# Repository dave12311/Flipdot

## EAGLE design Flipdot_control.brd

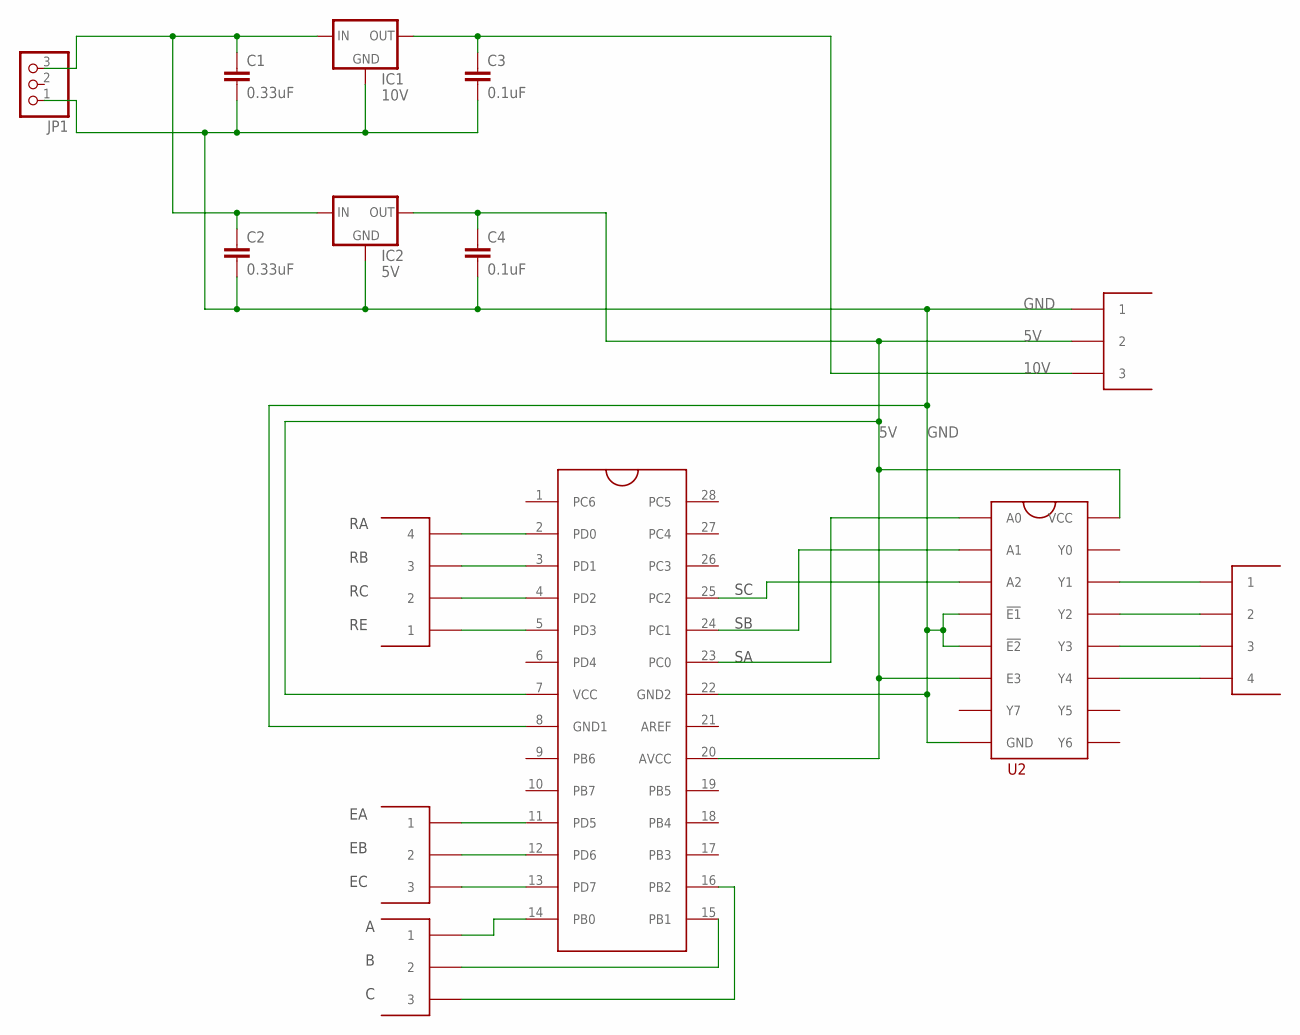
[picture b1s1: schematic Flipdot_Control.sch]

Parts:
C1, C2: 0.33uF; C025-024X044
C3, C4: 0.1uF; C025-024X044
IC1: 10V; 78XXS
IC2: 5V; 78XXS
JP1: PINHD-1X3; 1X03
U1: ATMEGA328P; DIL28
U2: 74HC238; DIL16
U$3, U$4: 4_PIN
U$5, U$6, U$7: 3_PIN

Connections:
5V: C4.1, IC2.OUT, U1.7 (VCC), U1.20 (AVCC), U2.6 (E3), U2.16 (VCC), U$7.P$2 (2)
10V: C3.1, IC1.OUT, U$7.P$3 (3)
GND: C1.2, C2.2, C3.2, C4.2, IC1.GND, IC2.GND, JP1.1, U1.8 (GND1), U1.22 (GND2), U2.4 (!E1), U2.5 (!E2), U2.8 (GND), U$7.P$1 (1)
unnamed: U2.14 (Y1), U$3.P$1 (1)
unnamed: U2.13 (Y2), U$3.P$2 (2)
unnamed: U2.12 (Y3), U$3.P$3 (3)
unnamed: U2.11 (Y4), U$3.P$4 (4)
unnamed: U1.23 (PC0), U2.1 (A0)
unnamed: U1.24 (PC1), U2.2 (A1)
unnamed: U1.25 (PC2), U2.3 (A2)
unnamed: U1.2 (PD0), U$4.P$4 (4)
unnamed: U1.3 (PD1), U$4.P$3 (3)
unnamed: U1.4 (PD2), U$4.P$2 (2)
unnamed: U1.14 (PB0), U$5.P$1 (1)
unnamed: U1.15 (PB1), U$5.P$2 (2)
unnamed: U1.16 (PB2), U$5.P$3 (3)
unnamed: U1.5 (PD3), U$4.P$1 (1)
unnamed: U1.13 (PD7), U$6.P$3 (3)
unnamed: U1.12 (PD6), U$6.P$2 (2)
unnamed: C1.1, C2.1, IC1.IN, IC2.IN, JP1.3
unnamed: U1.11 (PD5), U$6.P$1 (1)

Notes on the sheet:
A B C
RA RB RC RE
EA EB EC
SC SB SA

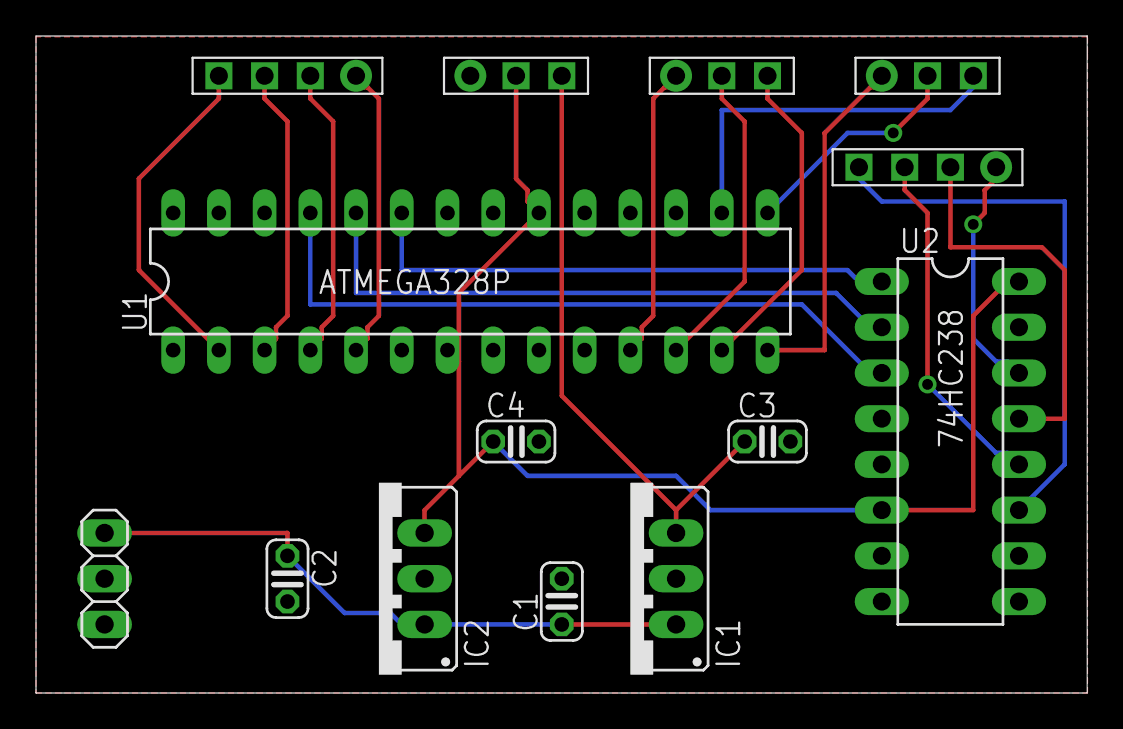
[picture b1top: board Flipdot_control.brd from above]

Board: 2 copper layers, 58.4 x 36.5 mm, 14 parts (0 on the bottom side), 21 nets.

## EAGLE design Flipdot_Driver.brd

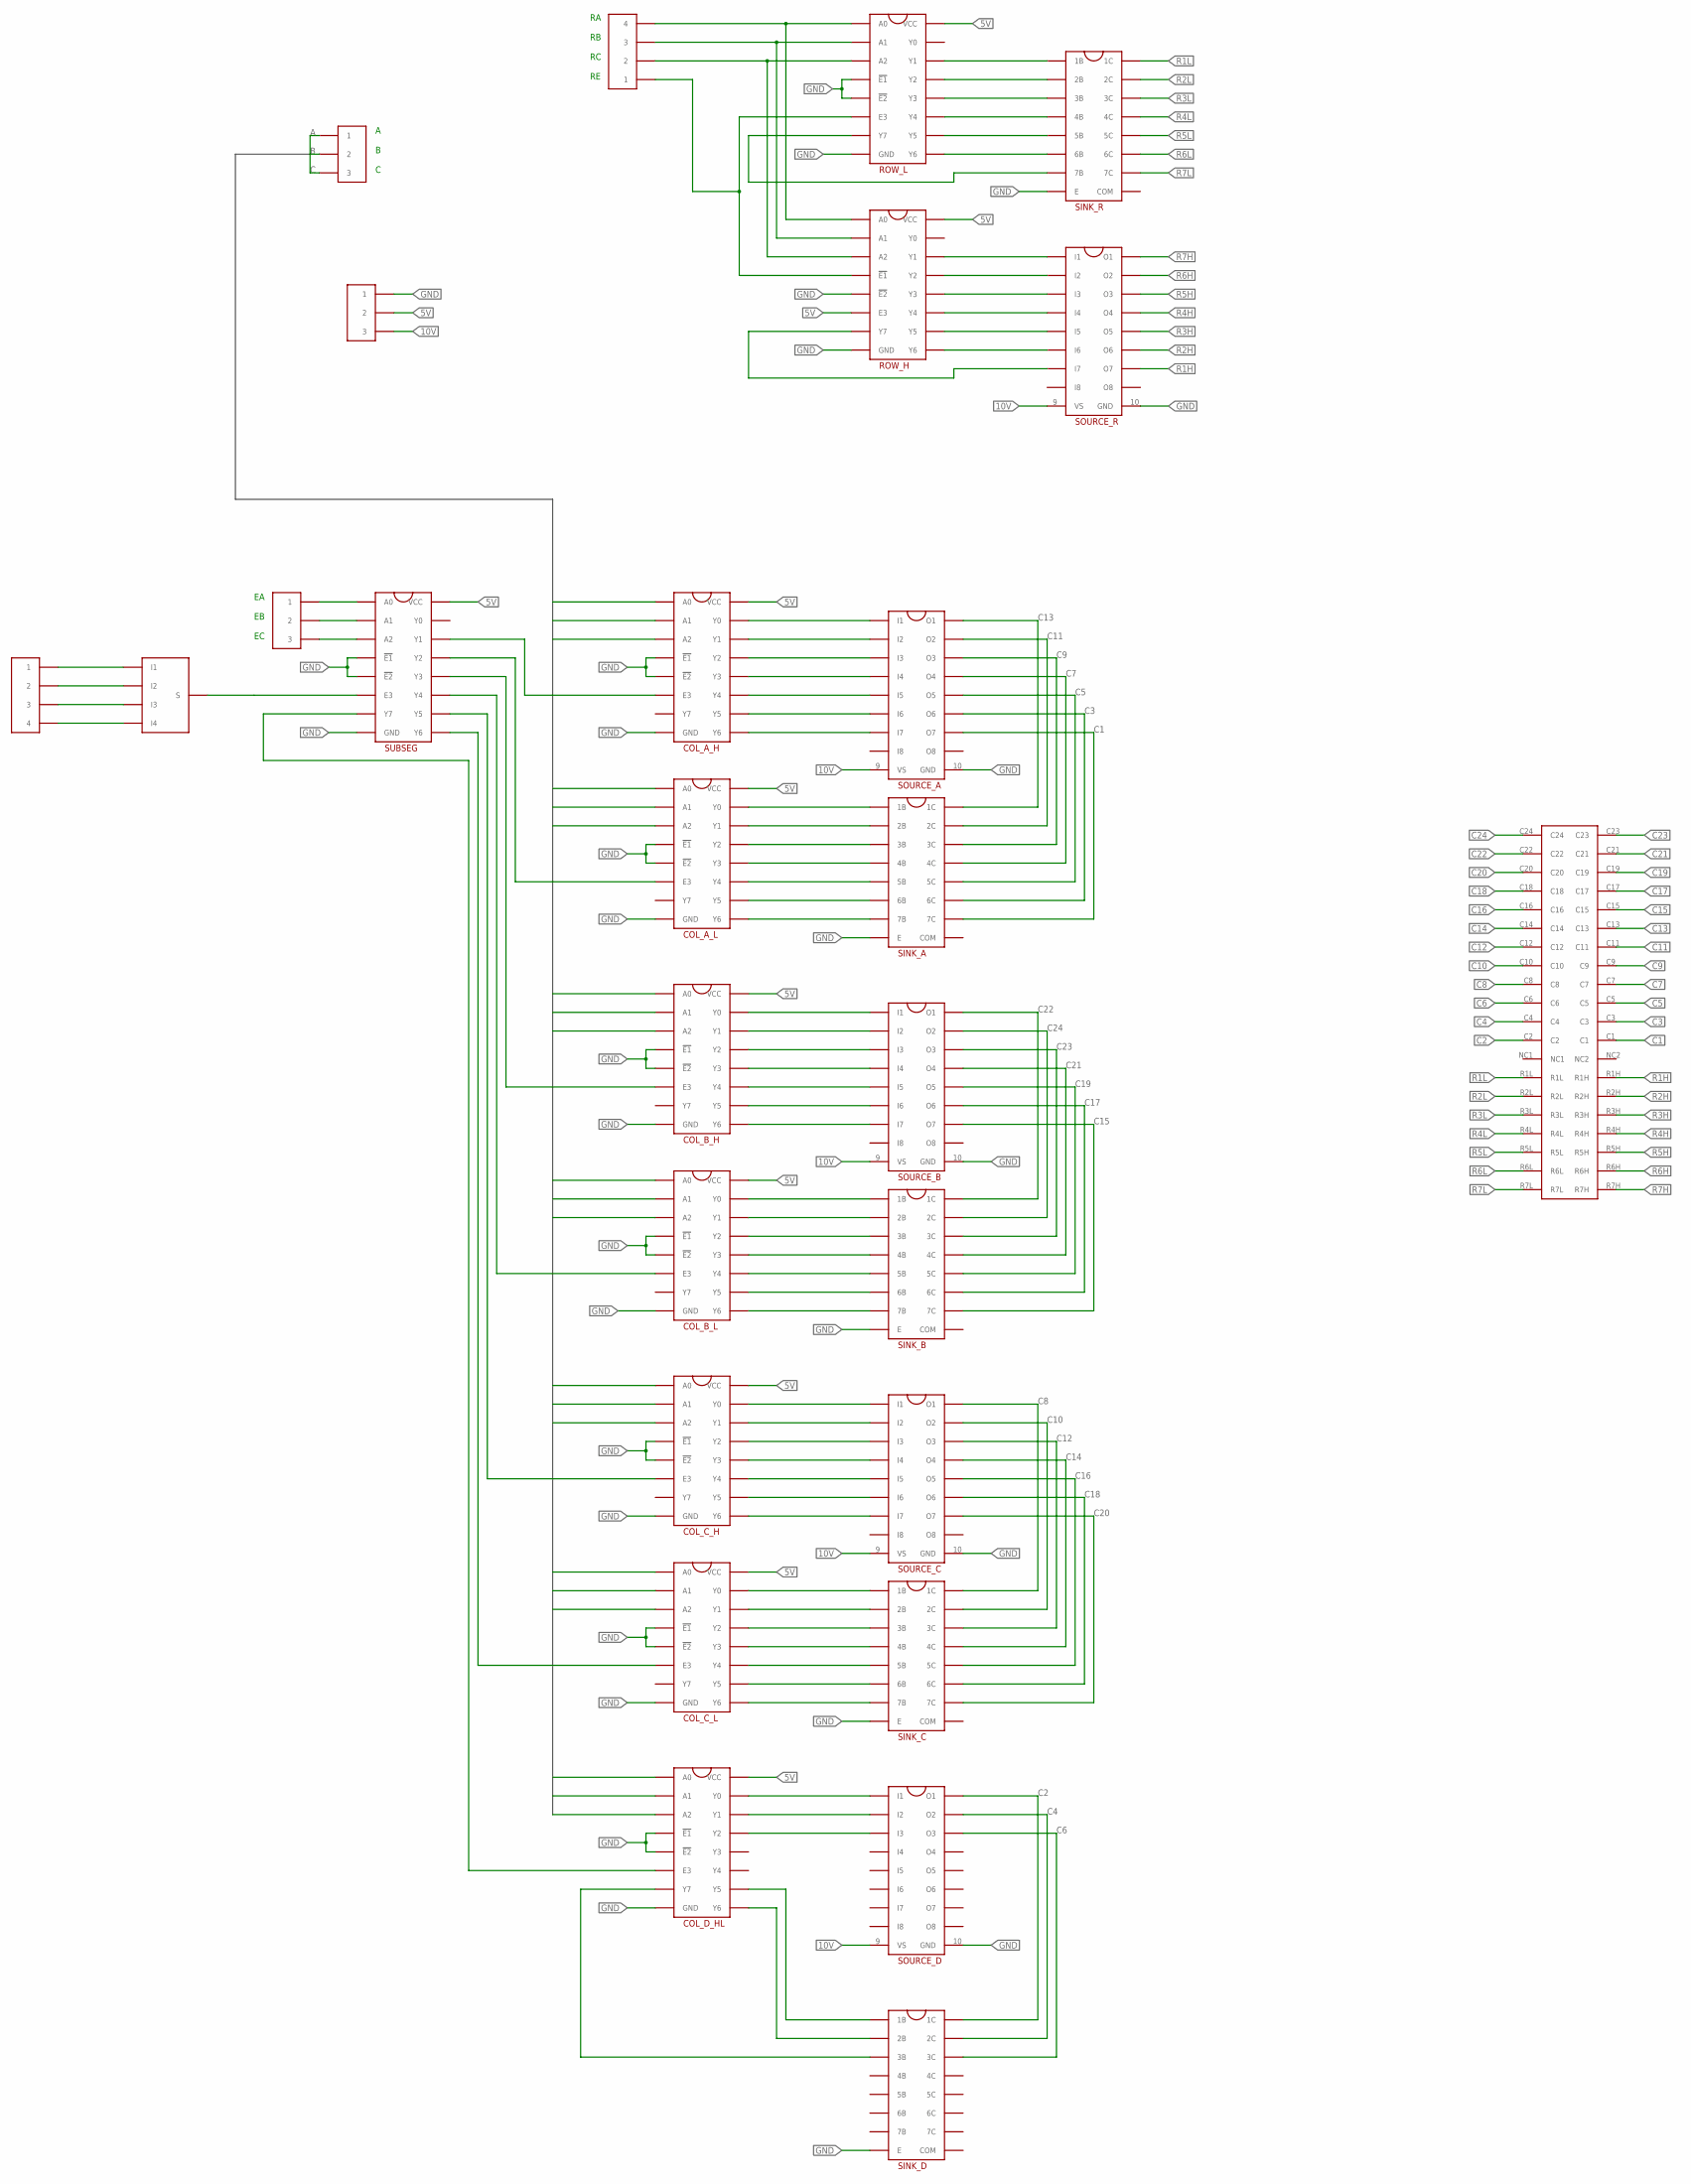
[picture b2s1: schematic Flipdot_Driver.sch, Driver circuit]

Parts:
COL_A_H: 74HC238; DIL16
COL_A_L: 74HC238; DIL16
COL_B_H: 74HC238; DIL16
COL_B_L: 74HC238; DIL16
COL_C_H: 74HC238; DIL16
COL_C_L: 74HC238; DIL16
COL_D_HL: 74HC238; DIL16
ROW_H: 74HC238; DIL16
ROW_L: 74HC238; DIL16
SINK_A: ULN2003A; DIL16
SINK_B: ULN2003A; DIL16
SINK_C: ULN2003A; DIL16
SINK_D: ULN2003A; DIL16
SINK_R: ULN2003A; DIL16
SOURCE_A: UDN2981A; DIL18
SOURCE_B: UDN2981A; DIL18
SOURCE_C: UDN2981A; DIL18
SOURCE_D: UDN2981A; DIL18
SOURCE_R: UDN2981A; DIL18
SUBSEG: 74HC238; DIL16
U$1: HEADER_40
U$2, U$3, U$5: 3_PIN
U$6, U$11: 4_PIN
U$10: JUMPER

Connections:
5V: COL_A_H.16 (VCC), COL_A_L.16 (VCC), COL_B_H.16 (VCC), COL_B_L.16 (VCC), COL_C_H.16 (VCC), COL_C_L.16 (VCC), COL_D_HL.16 (VCC), ROW_H.6 (E3), ROW_H.16 (VCC), ROW_L.16 (VCC), SUBSEG.16 (VCC), U$5.P$2 (2)
10V: SOURCE_A.9 (VS), SOURCE_B.9 (VS), SOURCE_C.9 (VS), SOURCE_D.9 (VS), SOURCE_R.9 (VS), U$5.P$3 (3)
A: COL_A_H.1 (A0), COL_A_L.1 (A0), COL_B_H.1 (A0), COL_B_L.1 (A0), COL_C_H.1 (A0), COL_C_L.1 (A0), COL_D_HL.1 (A0), U$2.P$1 (1)
B: COL_A_H.2 (A1), COL_A_L.2 (A1), COL_B_H.2 (A1), COL_B_L.2 (A1), COL_C_H.2 (A1), COL_C_L.2 (A1), COL_D_HL.2 (A1), U$2.P$2 (2)
C: COL_A_H.3 (A2), COL_A_L.3 (A2), COL_B_H.3 (A2), COL_B_L.3 (A2), COL_C_H.3 (A2), COL_C_L.3 (A2), COL_D_HL.3 (A2), U$2.P$3 (3)
C1: SINK_A.10 (7C), SOURCE_A.12 (O7), U$1.C1
C2: SINK_D.16 (1C), SOURCE_D.18 (O1), U$1.C2
C3: SINK_A.11 (6C), SOURCE_A.13 (O6), U$1.C3
C4: SINK_D.15 (2C), SOURCE_D.17 (O2), U$1.C4
C5: SINK_A.12 (5C), SOURCE_A.14 (O5), U$1.C5
C6: SINK_D.14 (3C), SOURCE_D.16 (O3), U$1.C6
C7: SINK_A.13 (4C), SOURCE_A.15 (O4), U$1.C7
C8: SINK_C.16 (1C), SOURCE_C.18 (O1), U$1.C8
C9: SINK_A.14 (3C), SOURCE_A.16 (O3), U$1.C9
C10: SINK_C.15 (2C), SOURCE_C.17 (O2), U$1.C10
C11: SINK_A.15 (2C), SOURCE_A.17 (O2), U$1.C11
C12: SINK_C.14 (3C), SOURCE_C.16 (O3), U$1.C12
C13: SINK_A.16 (1C), SOURCE_A.18 (O1), U$1.C13
C14: SINK_C.13 (4C), SOURCE_C.15 (O4), U$1.C14
C15: SINK_B.10 (7C), SOURCE_B.12 (O7), U$1.C15
C16: SINK_C.12 (5C), SOURCE_C.14 (O5), U$1.C16
C17: SINK_B.11 (6C), SOURCE_B.13 (O6), U$1.C17
C18: SINK_C.11 (6C), SOURCE_C.13 (O6), U$1.C18
C19: SINK_B.12 (5C), SOURCE_B.14 (O5), U$1.C19
C20: SINK_C.10 (7C), SOURCE_C.12 (O7), U$1.C20
C21: SINK_B.13 (4C), SOURCE_B.15 (O4), U$1.C21
C22: SINK_B.16 (1C), SOURCE_B.18 (O1), U$1.C22
C23: SINK_B.14 (3C), SOURCE_B.16 (O3), U$1.C23
C24: SINK_B.15 (2C), SOURCE_B.17 (O2), U$1.C24
GND: COL_A_H.4 (!E1), COL_A_H.5 (!E2), COL_A_H.8 (GND), COL_A_L.4 (!E1), COL_A_L.5 (!E2), COL_A_L.8 (GND), COL_B_H.4 (!E1), COL_B_H.5 (!E2), COL_B_H.8 (GND), COL_B_L.4 (!E1), COL_B_L.5 (!E2), COL_B_L.8 (GND), COL_C_H.4 (!E1), COL_C_H.5 (!E2), COL_C_H.8 (GND), COL_C_L.4 (!E1), COL_C_L.5 (!E2), COL_C_L.8 (GND), COL_D_HL.4 (!E1), COL_D_HL.5 (!E2), COL_D_HL.8 (GND), ROW_H.5 (!E2), ROW_H.8 (GND), ROW_L.4 (!E1), ROW_L.5 (!E2), ROW_L.8 (GND), SINK_A.8 (E), SINK_B.8 (E), SINK_C.8 (E), SINK_D.8 (E), SINK_R.8 (E), SOURCE_A.10 (GND), SOURCE_B.10 (GND), SOURCE_C.10 (GND), SOURCE_D.10 (GND), SOURCE_R.10 (GND), SUBSEG.4 (!E1), SUBSEG.5 (!E2), SUBSEG.8 (GND), U$5.P$1 (1)
unnamed: U$10.S1 (I1), U$11.P$1 (1)
unnamed: U$10.S2 (I2), U$11.P$2 (2)
unnamed: U$10.S3 (I3), U$11.P$3 (3)
unnamed: SUBSEG.1 (A0), U$3.P$1 (1)
unnamed: SUBSEG.2 (A1), U$3.P$2 (2)
unnamed: SUBSEG.3 (A2), U$3.P$3 (3)
unnamed: COL_A_L.6 (E3), SUBSEG.13 (Y2)
unnamed: COL_B_H.6 (E3), SUBSEG.12 (Y3)
unnamed: COL_A_H.6 (E3), SUBSEG.14 (Y1)
unnamed: COL_B_L.6 (E3), SUBSEG.11 (Y4)
unnamed: COL_C_H.6 (E3), SUBSEG.10 (Y5)
unnamed: COL_C_L.6 (E3), SUBSEG.9 (Y6)
unnamed: COL_D_HL.6 (E3), SUBSEG.7 (Y7)
unnamed: COL_A_H.15 (Y0), SOURCE_A.1 (I1)
unnamed: COL_A_H.14 (Y1), SOURCE_A.2 (I2)
unnamed: COL_A_H.13 (Y2), SOURCE_A.3 (I3)
unnamed: COL_A_H.12 (Y3), SOURCE_A.4 (I4)
unnamed: COL_A_H.11 (Y4), SOURCE_A.5 (I5)
unnamed: COL_A_H.10 (Y5), SOURCE_A.6 (I6)
unnamed: COL_A_H.9 (Y6), SOURCE_A.7 (I7)
unnamed: COL_B_H.15 (Y0), SOURCE_B.1 (I1)
unnamed: COL_B_H.14 (Y1), SOURCE_B.2 (I2)
unnamed: COL_B_H.13 (Y2), SOURCE_B.3 (I3)
unnamed: COL_B_H.12 (Y3), SOURCE_B.4 (I4)
unnamed: COL_B_H.11 (Y4), SOURCE_B.5 (I5)
unnamed: COL_B_H.10 (Y5), SOURCE_B.6 (I6)
unnamed: COL_B_H.9 (Y6), SOURCE_B.7 (I7)
unnamed: COL_C_H.15 (Y0), SOURCE_C.1 (I1)
unnamed: COL_C_H.14 (Y1), SOURCE_C.2 (I2)
unnamed: COL_C_H.13 (Y2), SOURCE_C.3 (I3)
unnamed: COL_C_H.12 (Y3), SOURCE_C.4 (I4)
unnamed: COL_C_H.11 (Y4), SOURCE_C.5 (I5)
unnamed: COL_C_H.10 (Y5), SOURCE_C.6 (I6)
unnamed: COL_C_H.9 (Y6), SOURCE_C.7 (I7)
unnamed: COL_D_HL.15 (Y0), SOURCE_D.1 (I1)
unnamed: COL_D_HL.14 (Y1), SOURCE_D.2 (I2)
unnamed: COL_D_HL.13 (Y2), SOURCE_D.3 (I3)
unnamed: COL_A_L.15 (Y0), SINK_A.1 (1B)
unnamed: COL_A_L.14 (Y1), SINK_A.2 (2B)
unnamed: COL_A_L.13 (Y2), SINK_A.3 (3B)
unnamed: COL_A_L.12 (Y3), SINK_A.4 (4B)
unnamed: COL_A_L.11 (Y4), SINK_A.5 (5B)
unnamed: COL_A_L.10 (Y5), SINK_A.6 (6B)
unnamed: COL_A_L.9 (Y6), SINK_A.7 (7B)
unnamed: COL_B_L.15 (Y0), SINK_B.1 (1B)
unnamed: COL_B_L.14 (Y1), SINK_B.2 (2B)
unnamed: COL_B_L.13 (Y2), SINK_B.3 (3B)
unnamed: COL_B_L.12 (Y3), SINK_B.4 (4B)
unnamed: COL_B_L.11 (Y4), SINK_B.5 (5B)
unnamed: COL_B_L.10 (Y5), SINK_B.6 (6B)
unnamed: COL_B_L.9 (Y6), SINK_B.7 (7B)
unnamed: COL_C_L.15 (Y0), SINK_C.1 (1B)
unnamed: COL_C_L.14 (Y1), SINK_C.2 (2B)
unnamed: COL_C_L.13 (Y2), SINK_C.3 (3B)
unnamed: COL_C_L.12 (Y3), SINK_C.4 (4B)
unnamed: COL_C_L.11 (Y4), SINK_C.5 (5B)
unnamed: COL_C_L.10 (Y5), SINK_C.6 (6B)
unnamed: COL_C_L.9 (Y6), SINK_C.7 (7B)
unnamed: COL_D_HL.10 (Y5), SINK_D.1 (1B)
unnamed: COL_D_HL.9 (Y6), SINK_D.2 (2B)
unnamed: COL_D_HL.7 (Y7), SINK_D.3 (3B)
unnamed: ROW_H.1 (A0), ROW_L.1 (A0), U$6.P$4 (4)
unnamed: ROW_H.2 (A1), ROW_L.2 (A1), U$6.P$3 (3)
unnamed: ROW_H.3 (A2), ROW_L.3 (A2), U$6.P$2 (2)
unnamed: ROW_H.4 (!E1), ROW_L.6 (E3), U$6.P$1 (1)
unnamed: ROW_L.14 (Y1), SINK_R.1 (1B)
unnamed: ROW_L.13 (Y2), SINK_R.2 (2B)
unnamed: ROW_L.12 (Y3), SINK_R.3 (3B)
unnamed: ROW_L.11 (Y4), SINK_R.4 (4B)
unnamed: ROW_L.10 (Y5), SINK_R.5 (5B)
unnamed: ROW_L.9 (Y6), SINK_R.6 (6B)
unnamed: ROW_L.7 (Y7), SINK_R.7 (7B)
unnamed: ROW_H.14 (Y1), SOURCE_R.1 (I1)
unnamed: ROW_H.13 (Y2), SOURCE_R.2 (I2)
unnamed: ROW_H.12 (Y3), SOURCE_R.3 (I3)
unnamed: ROW_H.11 (Y4), SOURCE_R.4 (I4)
unnamed: ROW_H.10 (Y5), SOURCE_R.5 (I5)
unnamed: ROW_H.9 (Y6), SOURCE_R.6 (I6)
unnamed: ROW_H.7 (Y7), SOURCE_R.7 (I7)
unnamed: U$10.S4 (I4), U$11.P$4 (4)
R1H: SOURCE_R.12 (O7), U$1.R1H
R1L: SINK_R.16 (1C), U$1.R1L
R2H: SOURCE_R.13 (O6), U$1.R2H
R2L: SINK_R.15 (2C), U$1.R2L
R3H: SOURCE_R.14 (O5), U$1.R3H
R3L: SINK_R.14 (3C), U$1.R3L
R4H: SOURCE_R.15 (O4), U$1.R4H
R4L: SINK_R.13 (4C), U$1.R4L
R5H: SOURCE_R.16 (O3), U$1.R5H
R5L: SINK_R.12 (5C), U$1.R5L
R6H: SOURCE_R.17 (O2), U$1.R6H
R6L: SINK_R.11 (6C), U$1.R6L
R7H: SOURCE_R.18 (O1), U$1.R7H
R7L: SINK_R.10 (7C), U$1.R7L
SEG_1: SUBSEG.6 (E3), U$10.X1 (S), U$10.X2 (S), U$10.X3 (S), U$10.X4 (S)

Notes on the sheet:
A B C
RA RB RC RE
EA EB EC

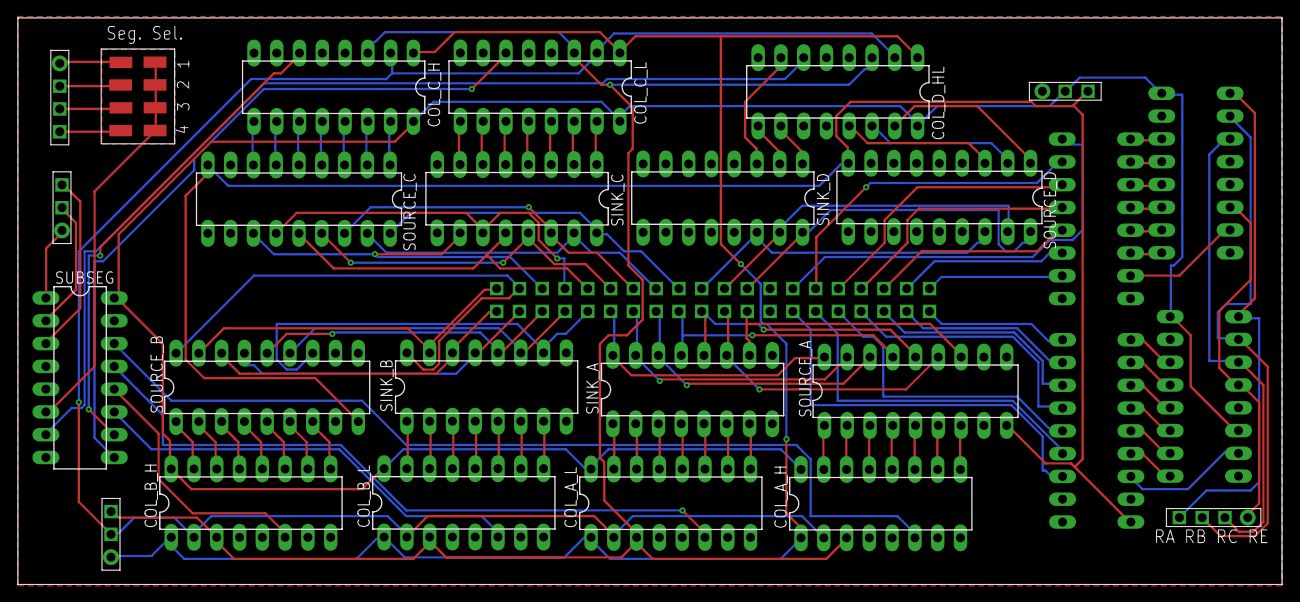
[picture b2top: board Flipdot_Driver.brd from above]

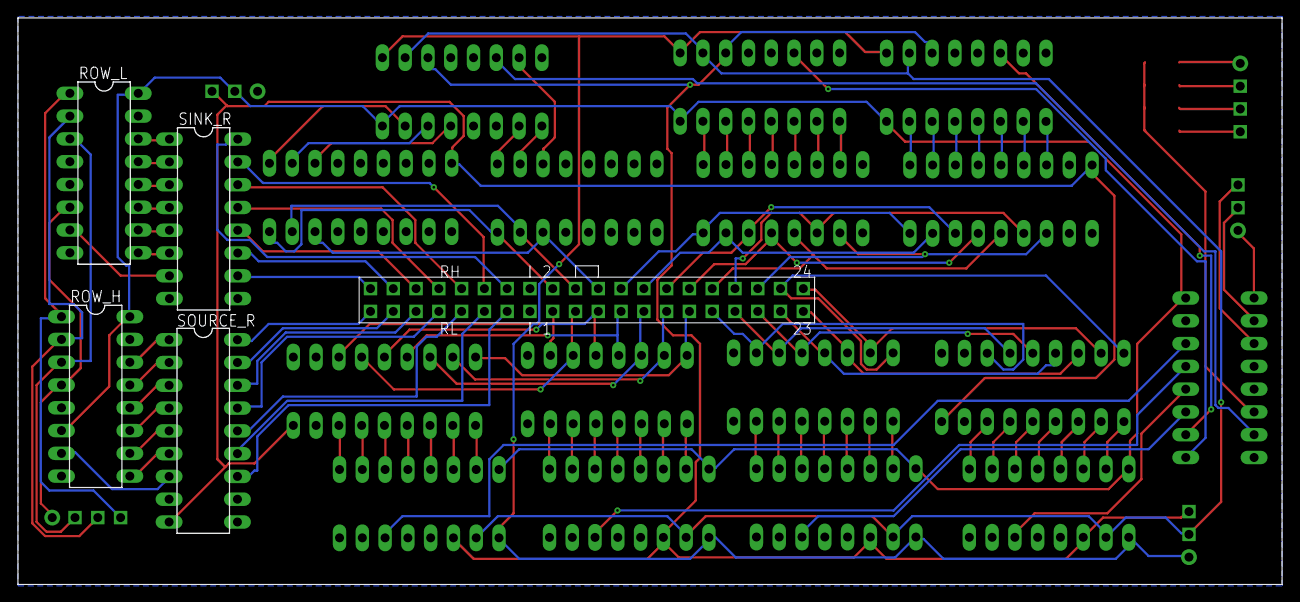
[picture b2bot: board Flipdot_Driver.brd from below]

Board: 2 copper layers, 140.9 x 63.2 mm, 27 parts (5 on the bottom side), 125 nets.

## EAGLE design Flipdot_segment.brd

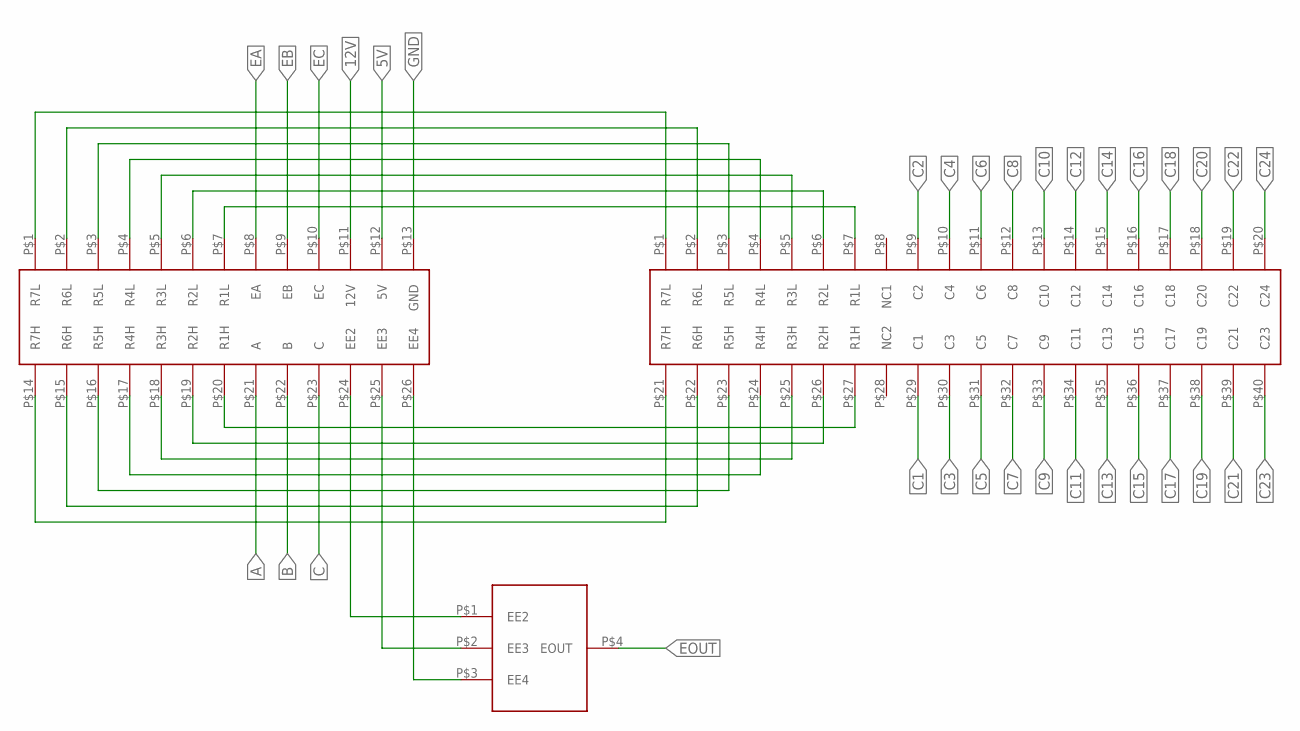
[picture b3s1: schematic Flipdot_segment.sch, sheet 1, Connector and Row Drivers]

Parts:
J1: HEADER
J2: HEADER_26
J3: JUMPER

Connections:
5V: J2.P$12 (5V); also elsewhere on the board
12V: J2.P$11 (12V); also elsewhere on the board
A: J2.P$21 (A); also elsewhere on the board
B: J2.P$22 (B); also elsewhere on the board
C: J2.P$23 (C); also elsewhere on the board
C1: J1.P$29 (C1); also elsewhere on the board
C2: J1.P$9 (C2); also elsewhere on the board
C3: J1.P$30 (C3); also elsewhere on the board
C4: J1.P$10 (C4); also elsewhere on the board
C5: J1.P$31 (C5); also elsewhere on the board
C6: J1.P$11 (C6); also elsewhere on the board
C7: J1.P$32 (C7); also elsewhere on the board
C8: J1.P$12 (C8); also elsewhere on the board
C9: J1.P$33 (C9); also elsewhere on the board
C10: J1.P$13 (C10); also elsewhere on the board
C11: J1.P$34 (C11); also elsewhere on the board
C12: J1.P$14 (C12); also elsewhere on the board
C13: J1.P$35 (C13); also elsewhere on the board
C14: J1.P$15 (C14); also elsewhere on the board
C15: J1.P$36 (C15); also elsewhere on the board
C16: J1.P$16 (C16); also elsewhere on the board
C17: J1.P$37 (C17); also elsewhere on the board
C18: J1.P$17 (C18); also elsewhere on the board
C19: J1.P$38 (C19); also elsewhere on the board
C20: J1.P$18 (C20); also elsewhere on the board
C21: J1.P$39 (C21); also elsewhere on the board
C22: J1.P$19 (C22); also elsewhere on the board
C23: J1.P$40 (C23); also elsewhere on the board
C24: J1.P$20 (C24); also elsewhere on the board
EA: J2.P$8 (EA); also elsewhere on the board
EB: J2.P$9 (EB); also elsewhere on the board
EC: J2.P$10 (EC); also elsewhere on the board
EE2: J2.P$24 (EE2), J3.P$1 (EE2)
EE3: J2.P$25 (EE3), J3.P$2 (EE3)
EE4: J2.P$26 (EE4), J3.P$3 (EE4)
EOUT: J3.P$4 (EOUT); also elsewhere on the board
GND: J2.P$13 (GND); also elsewhere on the board
unnamed: J1.P$7 (R1L), J2.P$7 (R1L)
unnamed: J1.P$6 (R2L), J2.P$6 (R2L)
unnamed: J1.P$5 (R3L), J2.P$5 (R3L)
unnamed: J1.P$4 (R4L), J2.P$4 (R4L)
unnamed: J1.P$3 (R5L), J2.P$3 (R5L)
unnamed: J1.P$2 (R6L), J2.P$2 (R6L)
unnamed: J1.P$1 (R7L), J2.P$1 (R7L)
unnamed: J1.P$27 (R1H), J2.P$20 (R1H)
unnamed: J1.P$26 (R2H), J2.P$19 (R2H)
unnamed: J1.P$25 (R3H), J2.P$18 (R3H)
unnamed: J1.P$24 (R4H), J2.P$17 (R4H)
unnamed: J1.P$23 (R5H), J2.P$16 (R5H)
unnamed: J1.P$22 (R6H), J2.P$15 (R6H)
unnamed: J1.P$21 (R7H), J2.P$14 (R7H)

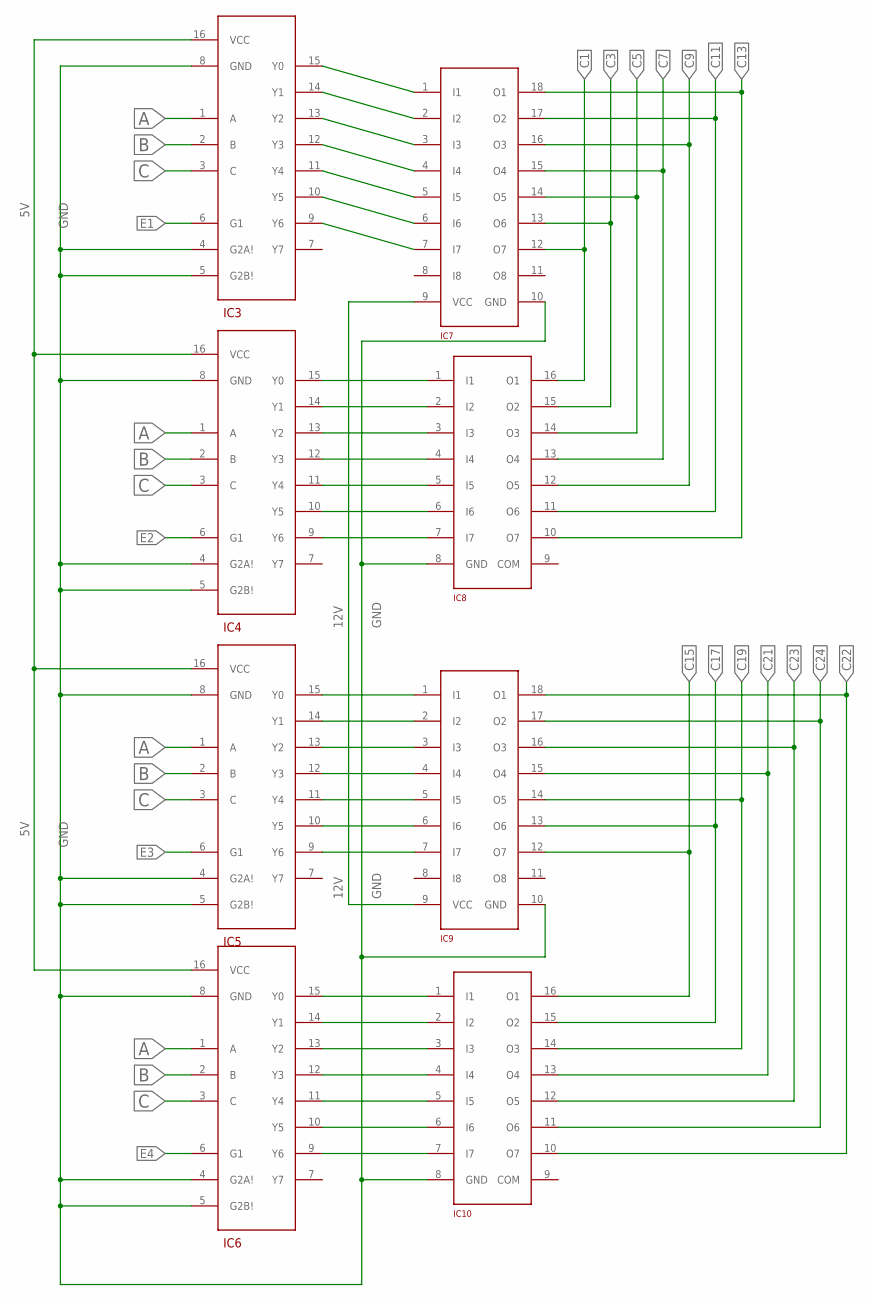
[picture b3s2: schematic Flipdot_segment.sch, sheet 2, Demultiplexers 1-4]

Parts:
IC3, IC4, IC5, IC6: M74HC238; SO16
IC7, IC9: TD62783_AFWG; SO18W
IC8, IC10: ULN2003; SO16

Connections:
5V: IC3.16 (VCC), IC4.16 (VCC), IC5.16 (VCC), IC6.16 (VCC); also elsewhere on the board
12V: IC7.9 (VCC), IC9.9 (VCC); also elsewhere on the board
A: IC3.1 (A), IC4.1 (A), IC5.1 (A), IC6.1 (A); also elsewhere on the board
B: IC3.2 (B), IC4.2 (B), IC5.2 (B), IC6.2 (B); also elsewhere on the board
C: IC3.3 (C), IC4.3 (C), IC5.3 (C), IC6.3 (C); also elsewhere on the board
C1: IC7.12 (O7), IC8.16 (O1); also elsewhere on the board
C3: IC7.13 (O6), IC8.15 (O2); also elsewhere on the board
C5: IC7.14 (O5), IC8.14 (O3); also elsewhere on the board
C7: IC7.15 (O4), IC8.13 (O4); also elsewhere on the board
C9: IC7.16 (O3), IC8.12 (O5); also elsewhere on the board
C11: IC7.17 (O2), IC8.11 (O6); also elsewhere on the board
C13: IC7.18 (O1), IC8.10 (O7); also elsewhere on the board
C15: IC9.12 (O7), IC10.16 (O1); also elsewhere on the board
C17: IC9.13 (O6), IC10.15 (O2); also elsewhere on the board
C19: IC9.14 (O5), IC10.14 (O3); also elsewhere on the board
C21: IC9.15 (O4), IC10.13 (O4); also elsewhere on the board
C22: IC9.18 (O1), IC10.10 (O7); also elsewhere on the board
C23: IC9.16 (O3), IC10.12 (O5); also elsewhere on the board
C24: IC9.17 (O2), IC10.11 (O6); also elsewhere on the board
E1: IC3.6 (G1); also elsewhere on the board
E2: IC4.6 (G1); also elsewhere on the board
E3: IC5.6 (G1); also elsewhere on the board
E4: IC6.6 (G1); also elsewhere on the board
GND: IC3.4 (G2A!), IC3.5 (G2B!), IC3.8 (GND), IC4.4 (G2A!), IC4.5 (G2B!), IC4.8 (GND), IC5.4 (G2A!), IC5.5 (G2B!), IC5.8 (GND), IC6.4 (G2A!), IC6.5 (G2B!), IC6.8 (GND), IC7.10 (GND), IC8.8 (GND), IC9.10 (GND), IC10.8 (GND); also elsewhere on the board
unnamed: IC3.15 (Y0), IC7.1 (I1)
unnamed: IC3.14 (Y1), IC7.2 (I2)
unnamed: IC3.13 (Y2), IC7.3 (I3)
unnamed: IC3.12 (Y3), IC7.4 (I4)
unnamed: IC3.11 (Y4), IC7.5 (I5)
unnamed: IC3.10 (Y5), IC7.6 (I6)
unnamed: IC3.9 (Y6), IC7.7 (I7)
unnamed: IC4.15 (Y0), IC8.1 (I1)
unnamed: IC4.14 (Y1), IC8.2 (I2)
unnamed: IC4.13 (Y2), IC8.3 (I3)
unnamed: IC4.12 (Y3), IC8.4 (I4)
unnamed: IC4.11 (Y4), IC8.5 (I5)
unnamed: IC4.10 (Y5), IC8.6 (I6)
unnamed: IC4.9 (Y6), IC8.7 (I7)
unnamed: IC5.15 (Y0), IC9.1 (I1)
unnamed: IC5.14 (Y1), IC9.2 (I2)
unnamed: IC5.13 (Y2), IC9.3 (I3)
unnamed: IC5.12 (Y3), IC9.4 (I4)
unnamed: IC5.11 (Y4), IC9.5 (I5)
unnamed: IC5.10 (Y5), IC9.6 (I6)
unnamed: IC5.9 (Y6), IC9.7 (I7)
unnamed: IC6.15 (Y0), IC10.1 (I1)
unnamed: IC6.14 (Y1), IC10.2 (I2)
unnamed: IC6.13 (Y2), IC10.3 (I3)
unnamed: IC6.12 (Y3), IC10.4 (I4)
unnamed: IC6.11 (Y4), IC10.5 (I5)
unnamed: IC6.10 (Y5), IC10.6 (I6)
unnamed: IC6.9 (Y6), IC10.7 (I7)

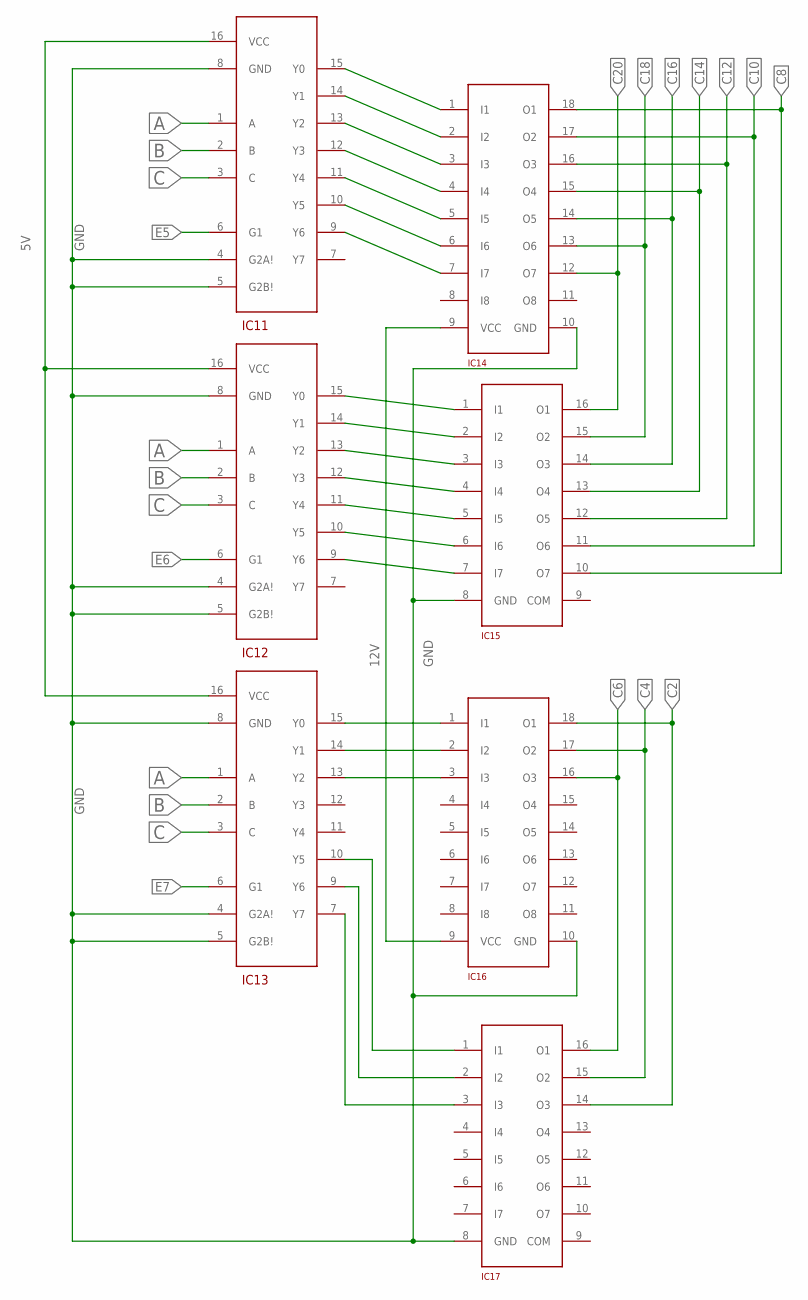
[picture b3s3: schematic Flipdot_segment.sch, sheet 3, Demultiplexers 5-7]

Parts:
IC11, IC12, IC13: M74HC238; SO16
IC14, IC16: TD62783_AFWG; SO18W
IC15, IC17: ULN2003; SO16

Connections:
5V: IC11.16 (VCC), IC12.16 (VCC), IC13.16 (VCC); also elsewhere on the board
12V: IC14.9 (VCC), IC16.9 (VCC); also elsewhere on the board
A: IC11.1 (A), IC12.1 (A), IC13.1 (A); also elsewhere on the board
B: IC11.2 (B), IC12.2 (B), IC13.2 (B); also elsewhere on the board
C: IC11.3 (C), IC12.3 (C), IC13.3 (C); also elsewhere on the board
C2: IC16.18 (O1), IC17.14 (O3); also elsewhere on the board
C4: IC16.17 (O2), IC17.15 (O2); also elsewhere on the board
C6: IC16.16 (O3), IC17.16 (O1); also elsewhere on the board
C8: IC14.18 (O1), IC15.10 (O7); also elsewhere on the board
C10: IC14.17 (O2), IC15.11 (O6); also elsewhere on the board
C12: IC14.16 (O3), IC15.12 (O5); also elsewhere on the board
C14: IC14.15 (O4), IC15.13 (O4); also elsewhere on the board
C16: IC14.14 (O5), IC15.14 (O3); also elsewhere on the board
C18: IC14.13 (O6), IC15.15 (O2); also elsewhere on the board
C20: IC14.12 (O7), IC15.16 (O1); also elsewhere on the board
E5: IC11.6 (G1); also elsewhere on the board
E6: IC12.6 (G1); also elsewhere on the board
E7: IC13.6 (G1); also elsewhere on the board
GND: IC11.4 (G2A!), IC11.5 (G2B!), IC11.8 (GND), IC12.4 (G2A!), IC12.5 (G2B!), IC12.8 (GND), IC13.4 (G2A!), IC13.5 (G2B!), IC13.8 (GND), IC14.10 (GND), IC15.8 (GND), IC16.10 (GND), IC17.8 (GND); also elsewhere on the board
unnamed: IC11.15 (Y0), IC14.1 (I1)
unnamed: IC11.14 (Y1), IC14.2 (I2)
unnamed: IC11.13 (Y2), IC14.3 (I3)
unnamed: IC11.12 (Y3), IC14.4 (I4)
unnamed: IC11.11 (Y4), IC14.5 (I5)
unnamed: IC11.10 (Y5), IC14.6 (I6)
unnamed: IC11.9 (Y6), IC14.7 (I7)
unnamed: IC12.15 (Y0), IC15.1 (I1)
unnamed: IC12.14 (Y1), IC15.2 (I2)
unnamed: IC12.13 (Y2), IC15.3 (I3)
unnamed: IC12.12 (Y3), IC15.4 (I4)
unnamed: IC12.11 (Y4), IC15.5 (I5)
unnamed: IC12.10 (Y5), IC15.6 (I6)
unnamed: IC12.9 (Y6), IC15.7 (I7)
unnamed: IC13.15 (Y0), IC16.1 (I1)
unnamed: IC13.14 (Y1), IC16.2 (I2)
unnamed: IC13.13 (Y2), IC16.3 (I3)
unnamed: IC13.10 (Y5), IC17.1 (I1)
unnamed: IC13.9 (Y6), IC17.2 (I2)
unnamed: IC13.7 (Y7), IC17.3 (I3)

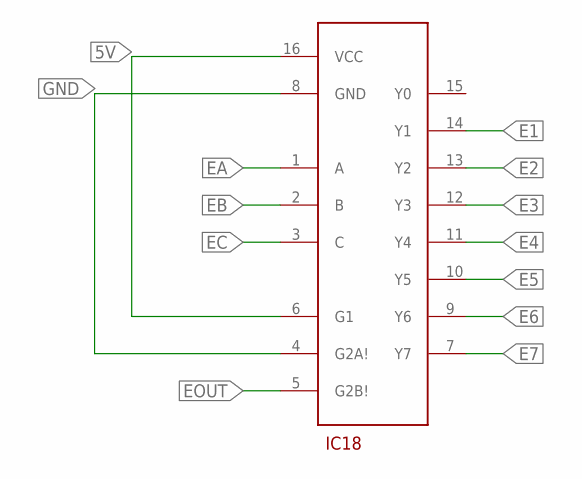
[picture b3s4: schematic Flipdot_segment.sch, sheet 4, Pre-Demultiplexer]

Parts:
IC18: M74HC238; SO16

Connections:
5V: IC18.6 (G1), IC18.16 (VCC); also elsewhere on the board
E1: IC18.14 (Y1); also elsewhere on the board
E2: IC18.13 (Y2); also elsewhere on the board
E3: IC18.12 (Y3); also elsewhere on the board
E4: IC18.11 (Y4); also elsewhere on the board
E5: IC18.10 (Y5); also elsewhere on the board
E6: IC18.9 (Y6); also elsewhere on the board
E7: IC18.7 (Y7); also elsewhere on the board
EA: IC18.1 (A); also elsewhere on the board
EB: IC18.2 (B); also elsewhere on the board
EC: IC18.3 (C); also elsewhere on the board
EOUT: IC18.5 (G2B!); also elsewhere on the board
GND: IC18.4 (G2A!), IC18.8 (GND); also elsewhere on the board

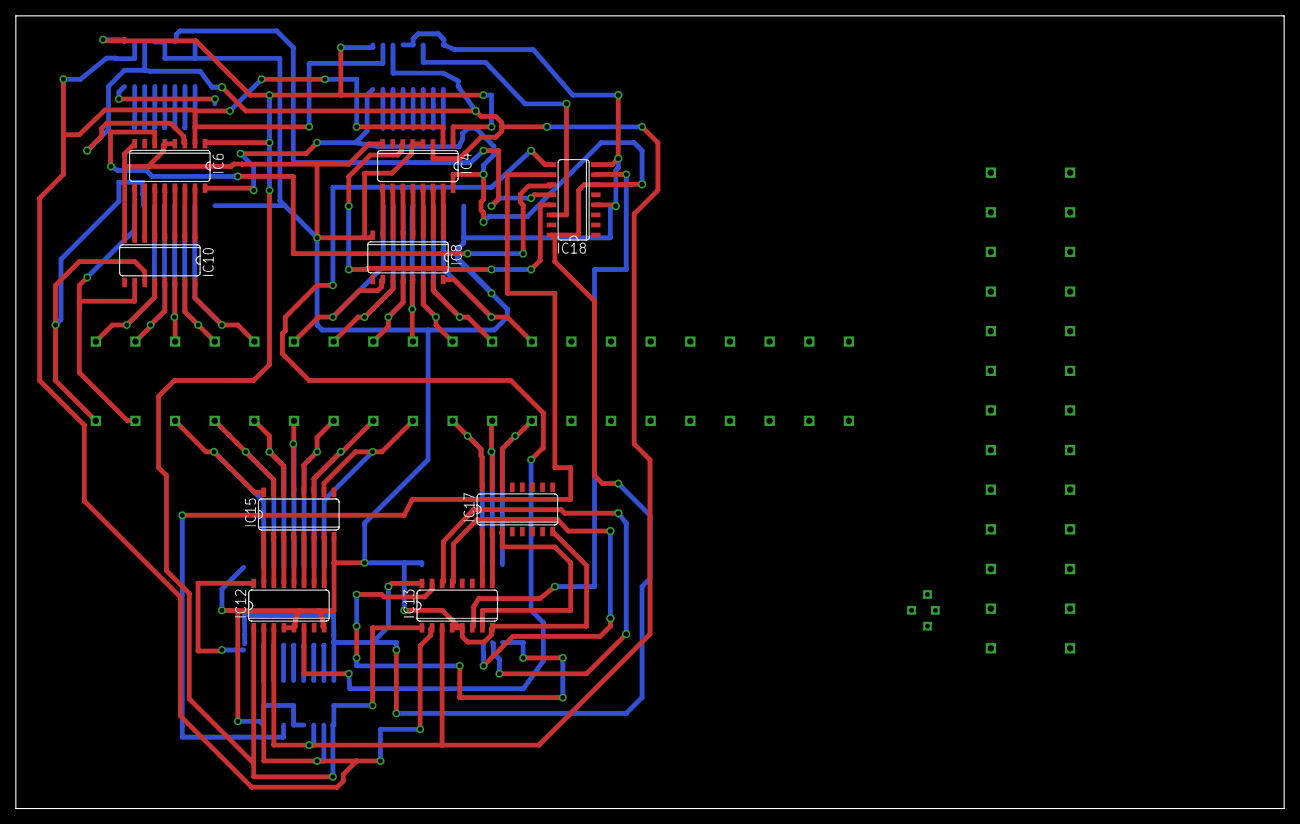
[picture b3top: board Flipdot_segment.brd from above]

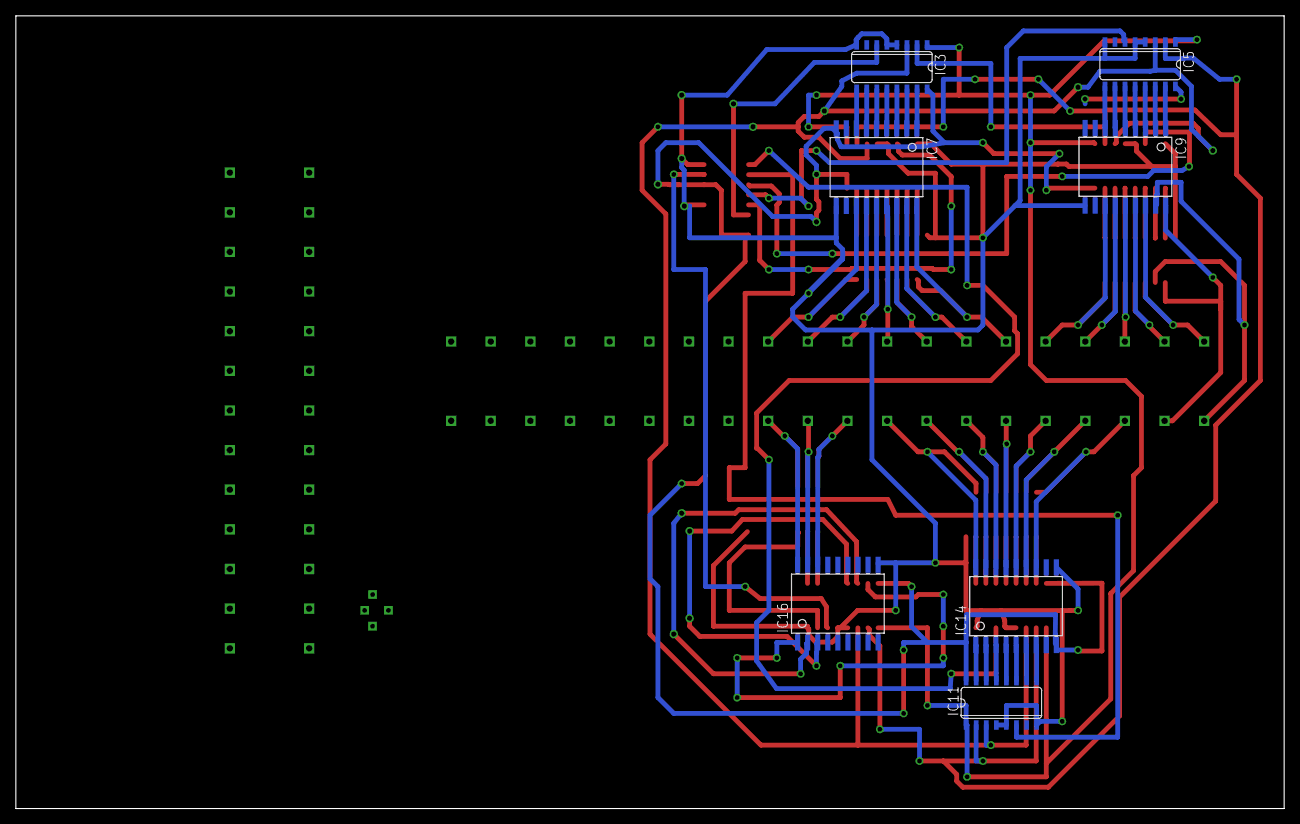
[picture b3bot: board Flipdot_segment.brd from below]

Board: 2 copper layers, 160.0 x 100.0 mm, 19 parts (7 on the bottom side), 106 nets.
